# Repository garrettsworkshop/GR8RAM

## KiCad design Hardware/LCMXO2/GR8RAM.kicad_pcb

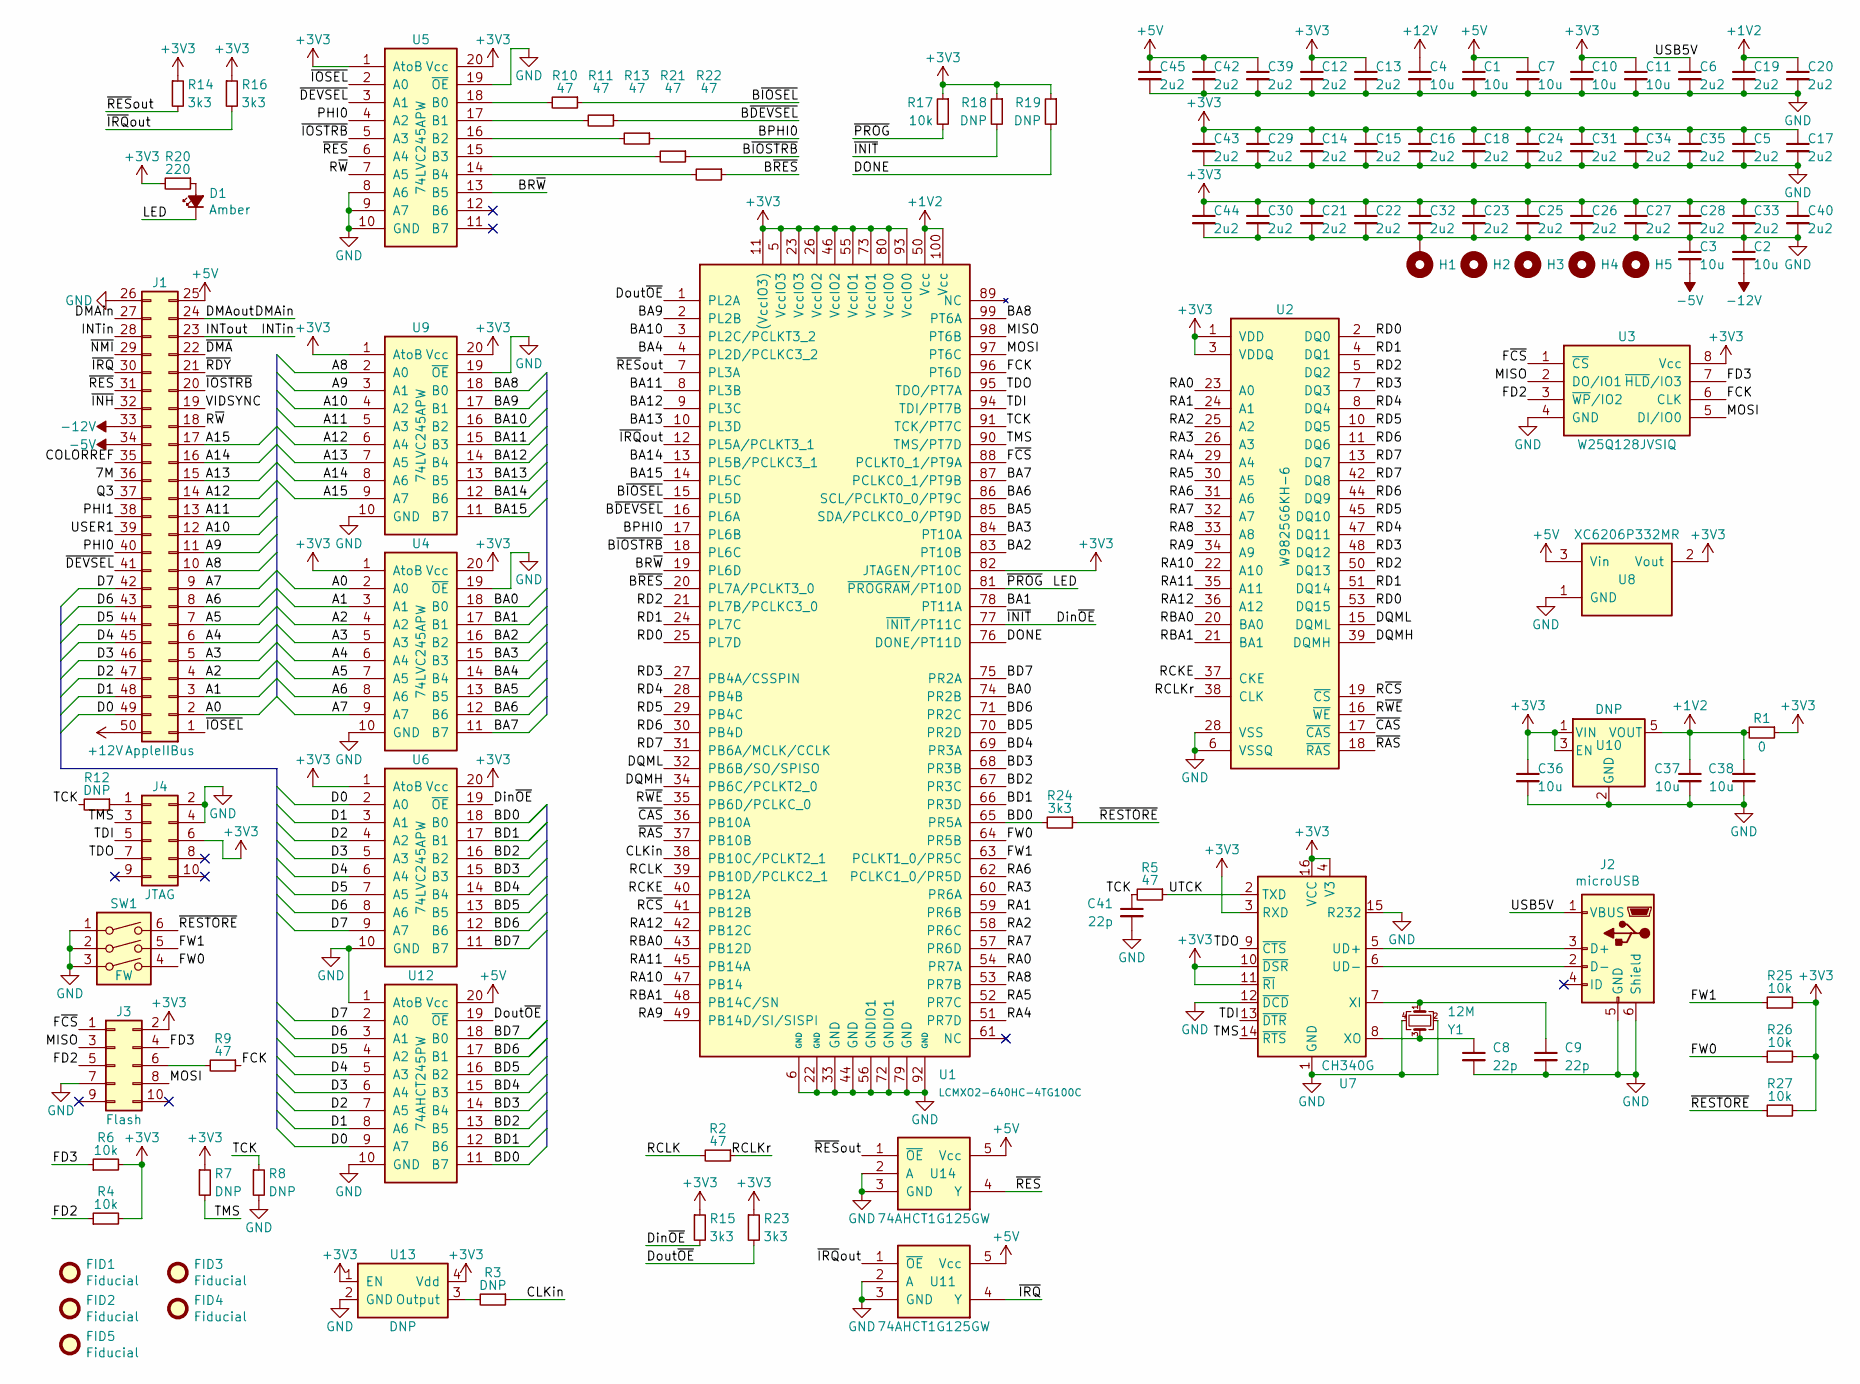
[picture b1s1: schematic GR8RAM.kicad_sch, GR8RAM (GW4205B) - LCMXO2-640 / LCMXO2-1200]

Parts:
C1, C2, C3, C4, C7, C10, C11, C36, C37, C38: 10u; C_0805; LCSC Part C15850
C5, C6, C12, C13, C14, C15, C16, C17, C18, C19, C20, C21, C22, C23, C24, C25, C26, C27, C28, C29, C30, C31, C32, C33, C34, C35, C39, C40, C42, C43, C44, C45: 2u2; C_0603; LCSC Part C23630
C8, C9, C41: 22p; C_0603; LCSC Part C1653
D1: Amber; LED_0805; LCSC Part C284932
FID1, FID2, FID3, FID4, FID5: Fiducial
H1: PasteHole_1.1mm_PTH
H2, H3, H4, H5: PasteHole_1.152mm_NPTH
J1: AppleIIBus; AppleIIBus_Edge
J2: microUSB; USB_Micro-B_Amphenol_10118192-0001; LCSC Part C132564
J3: Flash; Tag-Connect_TC2050-IDC-FP_2x05_P1.27mm_Vertical
J4: JTAG; Tag-Connect_TC2050-IDC-FP_2x05_P1.27mm_Vertical
R1: 0; R_0805; LCSC Part C17477
R2, R5, R9, R10, R11, R13, R21, R22: 47; R_0603; LCSC Part C23182
R3, R7, R8, R12, R18, R19: DNP; R_0603
R4, R6, R17, R25, R26, R27: 10k; R_0603; LCSC Part C25804
R14, R15, R16, R23, R24: 3k3; R_0603; LCSC Part C22978
R20: 220; R_0805; LCSC Part C17557
SW1: FW; SW_DIP_SPSTx03_Slide_DSHP03TS_P1.27mm; LCSC Part C319051
U1: LCMXO2-640HC-4TG100C; TQFP-100_14x14mm_P0.5mm; LCSC Part C1519051
U2: W9825G6KH-6; TSOP-II-54_22.2x10.16mm_P0.8mm; LCSC Part C62246
U3: W25Q128JVSIQ; SOIC-8_5.3mm; LCSC Part C97521
U4, U5, U6, U9: 74LVC245APW; TSSOP-20_4.4x6.5mm_P0.65mm; LCSC Part C6082
U7: CH340G; SOIC-16_3.9mm; LCSC Part C14267
U8: XC6206P332MR; SOT-23; LCSC Part C5446
U10: DNP; SOT-23-5
U11, U14: 74AHCT1G125GW; SOT-353; LCSC Part C12495
U12: 74AHCT245PW; TSSOP-20_4.4x6.5mm_P0.65mm; LCSC Part C173388
U13: DNP; Crystal_SMD_3225-4Pin_3.2x2.5mm
Y1: 12M; Crystal_SMD_3225-4Pin_3.2x2.5mm; LCSC Part C9002

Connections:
+1V2: C19.1, C20.1, C37.1, C38.1, R1.2, U1.50 (Vcc), U1.100 (Vcc), U10.5 (VOUT)
+3V3: C5.1, C10.1, C11.1, C12.1, C13.1, C14.1, C15.1, C16.1, C17.1, C18.1, C21.1, C22.1, C23.1, C24.1, C25.1, C26.1, C27.1, C28.1, C29.1, C30.1, C31.1, C32.1, C33.1, C34.1, C35.1, C36.1, C40.1, C43.1, C44.1, J3.2, J4.6, R1.1, R4.2, R6.2, R7.1, R14.1, R15.1, R16.1, R17.1, R18.1, R19.1, R20.2, R23.1, R25.2, R26.2, R27.2, U1.5 (VccIO3), U1.11 ((VccIO3)), U1.23 (VccIO3), U1.26 (VccIO2), U1.46 (VccIO2), U1.55 (VccIO1), U1.73 (VccIO1), U1.80 (VccIO0), U1.82 (JTAGEN/PT10C), U1.93 (VccIO0), U2.1 (VDD), U2.3 (VDDQ), U2.9 (VDDQ), U2.14 (VDD), U2.27 (VDD), U2.43 (VDDQ), U2.49 (VDDQ), U3.8 (Vcc), U4.1 (AtoB), U4.20 (Vcc), U5.1 (AtoB), U5.20 (Vcc), U6.1 (AtoB), U6.20 (Vcc), U7.3 (RXD), U7.4 (V3), U7.10 (~DSR), U7.11 (~RI), U7.16 (VCC), U8.2 (Vout), U9.1 (AtoB), U9.20 (Vcc), U10.1 (VIN), U10.3 (EN), U13.1 (EN), U13.4 (Vdd)
+5V: C1.1, C7.1, C39.1, C42.1, C45.1, J1.25, U8.3 (Vin), U11.5 (Vcc), U12.20 (Vcc), U14.5 (Vcc)
+12V: C4.1, J1.50
-5V: C3.2, J1.34
-12V: C2.2, J1.33
/7M: J1.36
/A0: J1.2, U4.2 (A0)
/A1: J1.3, U4.3 (A1)
/A2: J1.4, U4.4 (A2)
/A3: J1.5, U4.5 (A3)
/A4: J1.6, U4.6 (A4)
/A5: J1.7, U4.7 (A5)
/A6: J1.8, U4.8 (A6)
/A7: J1.9, U4.9 (A7)
/A8: J1.10, U9.2 (A0)
/A9: J1.11, U9.3 (A1)
/A10: J1.12, U9.4 (A2)
/A11: J1.13, U9.5 (A3)
/A12: J1.14, U9.6 (A4)
/A13: J1.15, U9.7 (A5)
/A14: J1.16, U9.8 (A6)
/A15: J1.17, U9.9 (A7)
/BA0: U1.74 (PR2B), U4.18 (B0)
/BA1: U1.78 (PT11A), U4.17 (B1)
/BA2: U1.83 (PT10B), U4.16 (B2)
/BA3: U1.84 (PT10A), U4.15 (B3)
/BA4: U1.4 (PL2D/PCLKC3_2), U4.14 (B4)
/BA5: U1.85 (SDA/PCLKC0_0/PT9D), U4.13 (B5)
/BA6: U1.86 (SCL/PCLKT0_0/PT9C), U4.12 (B6)
/BA7: U1.87 (PCLKC0_1/PT9B), U4.11 (B7)
/BA8: U1.99 (PT6A), U9.18 (B0)
/BA9: U1.2 (PL2B), U9.17 (B1)
/BA10: U1.3 (PL2C/PCLKT3_2), U9.16 (B2)
/BA11: U1.8 (PL3B), U9.15 (B3)
/BA12: U1.9 (PL3C), U9.14 (B4)
/BA13: U1.10 (PL3D), U9.13 (B5)
/BA14: U1.13 (PL5B/PCLKC3_1), U9.12 (B6)
/BA15: U1.14 (PL5C), U9.11 (B7)
/BD0: R24.2, U1.65 (PR5A), U6.18 (B0), U12.11 (B7)
/BD1: U1.66 (PR3D), U6.17 (B1), U12.12 (B6)
/BD2: U1.67 (PR3C), U6.16 (B2), U12.13 (B5)
/BD3: U1.68 (PR3B), U6.15 (B3), U12.14 (B4)
/BD4: U1.69 (PR3A), U6.14 (B4), U12.15 (B3)
/BD5: U1.70 (PR2D), U6.13 (B5), U12.16 (B2)
/BD6: U1.71 (PR2C), U6.12 (B6), U12.17 (B1)
/BD7: U1.75 (PR2A), U6.11 (B7), U12.18 (B0)
/BPHI0: R13.1, U1.17 (PL6B)
/BR~W: U1.19 (PL6D), U5.13 (B5)
/B~DEVSEL: R11.1, U1.16 (PL6A)
/B~IOSEL: R10.1, U1.15 (PL5D)
/B~IOSTRB: R21.1, U1.18 (PL6C)
/B~RES: R22.1, U1.20 (PL7A/PCLKT3_0)
/CLKin: R3.1, U1.38 (PB10C/PCLKT2_1)
/COLORREF: J1.35
/D0: J1.49, U6.2 (A0), U12.9 (A7)
/D1: J1.48, U6.3 (A1), U12.8 (A6)
/D2: J1.47, U6.4 (A2), U12.7 (A5)
/D3: J1.46, U6.5 (A3), U12.6 (A4)
/D4: J1.45, U6.6 (A4), U12.5 (A3)
/D5: J1.44, U6.7 (A5), U12.4 (A2)
/D6: J1.43, U6.8 (A6), U12.3 (A1)
/D7: J1.42, U6.9 (A7), U12.2 (A0)
/DMAin: J1.24, J1.27
/DONE: R19.2, U1.76 (DONE/PT11D)
/DQMH: U1.34 (PB6C/PCLKT2_0), U2.39 (DQMH)
/DQML: U1.32 (PB6B/SO/SPISO), U2.15 (DQML)
/Din~OE: R15.2, R18.2, U1.77 (~INIT/PT11C), U6.19 (~OE)
/Dout~OE: R23.2, U1.1 (PL2A), U12.19 (~OE)
/FCK: R9.1, U1.96 (PT6D), U3.6 (CLK)
/FD2: J3.5, R4.1, U3.3 (~WP/IO2)
/FD3: J3.4, R6.1, U3.7 (~HLD/IO3)
/FW0: R26.1, SW1.4, U1.64 (PR5B)
/FW1: R25.1, SW1.5, U1.63 (PCLKT1_0/PR5C)
/F~CS: J3.1, U1.88 (PCLKT0_1/PT9A), U3.1 (~CS)
/INTin: J1.23, J1.28
/LED: D1.1 (K), R17.2, U1.81 (~PROGRAM/PT10D)
/MISO: J3.3, U1.98 (PT6B), U3.2 (DO/IO1)
/MOSI: J3.8, U1.97 (PT6C), U3.5 (DI/IO0)
/PHI0: J1.40, U5.4 (A2)
/PHI1: J1.38
/Q3: J1.37
/RA0: U1.54 (PR7A), U2.23 (A0)
/RA1: U1.59 (PR6B), U2.24 (A1)
/RA2: U1.58 (PR6C), U2.25 (A2)
/RA3: U1.60 (PR6A), U2.26 (A3)
/RA4: U1.51 (PR7D), U2.29 (A4)
/RA5: U1.52 (PR7C), U2.30 (A5)
/RA6: U1.62 (PCLKC1_0/PR5D), U2.31 (A6)
/RA7: U1.57 (PR6D), U2.32 (A7)
/RA8: U1.53 (PR7B), U2.33 (A8)
/RA9: U1.49 (PB14D/SI/SISPI), U2.34 (A9)
/RA10: U1.47 (PB14), U2.22 (A10)
/RA11: U1.45 (PB14A), U2.35 (A11)
/RA12: U1.42 (PB12C), U2.36 (A12)
/RBA0: U1.43 (PB12D), U2.20 (BA0)
/RBA1: U1.48 (PB14C/SN), U2.21 (BA1)
/RCKE: U1.40 (PB12A), U2.37 (CKE)
/RCLK: R2.2, U1.39 (PB10D/PCLKC2_1)
/RCLKr: R2.1, U2.38 (CLK)
/RD0: U1.25 (PL7D), U2.2 (DQ0), U2.53 (DQ15)
/RD1: U1.24 (PL7C), U2.4 (DQ1), U2.51 (DQ14)
/RD2: U1.21 (PL7B/PCLKC3_0), U2.5 (DQ2), U2.50 (DQ13)
/RD3: U1.27 (PB4A/CSSPIN), U2.7 (DQ3), U2.48 (DQ12)
/RD4: U1.28 (PB4B), U2.8 (DQ4), U2.47 (DQ11)
/RD5: U1.29 (PB4C), U2.10 (DQ5), U2.45 (DQ10)
/RD6: U1.30 (PB4D), U2.11 (DQ6), U2.44 (DQ9)
/RD7: U1.31 (PB6A/MCLK/CCLK), U2.13 (DQ7), U2.42 (DQ8)
/R~CS: U1.41 (PB12B), U2.19 (~CS)
/R~WE: U1.35 (PB6D/PCLKC_0), U2.16 (~WE)
/R~W: J1.18, U5.7 (A5)
/TCK: C41.1, R5.2, R8.1, R12.2, U1.91 (TCK/PT7C)
/TDI: J4.5, U1.94 (TDI/PT7B), U7.13 (~DTR)
/TDO: J4.7, U1.95 (TDO/PT7A), U7.9 (~CTS)
/TMS: J4.3, R7.2, U1.90 (TMS/PT7D), U7.14 (~RTS)
/USB5V: C6.1, J2.1 (VBUS)
/USER1: J1.39
/UTCK: R5.1, U7.2 (TXD)
/VIDSYNC: J1.19
/~CAS: U1.36 (PB10A), U2.17 (~CAS)
/~DEVSEL: J1.41, U5.3 (A1)
/~DMA: J1.22
/~INH: J1.32
/~IOSEL: J1.1, U5.2 (A0)
/~IOSTRB: J1.20, U5.5 (A3)
/~IRQ: J1.30, U11.4 (Y)
/~IRQout: R16.2, U1.12 (PL5A/PCLKT3_1), U11.1 (~OE)
/~NMI: J1.29
/~RAS: U1.37 (PB10B), U2.18 (~RAS)
/~RDY: J1.21
/~RESTORE: R24.1, R27.1, SW1.6
/~RES: J1.31, U5.6 (A4), U14.4 (Y)
/~RESout: R14.2, U1.7 (PL3A), U14.1 (~OE)
GND: C1.2, C2.1, C3.1, C4.2, C5.2, C6.2, C7.2, C8.2, C9.2, C10.2, C11.2, C12.2, C13.2, C14.2, C15.2, C16.2, C17.2, C18.2, C19.2, C20.2, C21.2, C22.2, C23.2, C24.2, C25.2, C26.2, C27.2, C28.2, C29.2, C30.2, C31.2, C32.2, C33.2, C34.2, C35.2, C36.2, C37.2, C38.2, C39.2, C40.2, C41.2, C42.2, C43.2, C44.2, C45.2, H1.1, J1.26, J2.5 (GND), J2.6 (Shield), J3.7, J4.2, J4.4, R8.2, SW1.1, SW1.2, SW1.3, U1.6 (GND), U1.22 (GND), U1.33 (GND), U1.44 (GND), U1.56 (GNDIO1), U1.72 (GNDIO1), U1.79 (GND), U1.92 (GND), U2.6 (VSSQ), U2.12 (VSSQ), U2.28 (VSS), U2.41 (VSS), U2.46 (VSSQ), U2.52 (VSSQ), U2.54 (VSS), U3.4 (GND), U4.10 (GND), U4.19 (~OE), U5.8 (A6), U5.9 (A7), U5.10 (GND), U5.19 (~OE), U6.10 (GND), U7.1 (GND), U7.12 (~DCD), U7.15 (R232), U8.1 (GND), U9.10 (GND), U9.19 (~OE), U10.2 (GND), U11.2 (A), U11.3 (GND), U12.1 (AtoB), U12.10 (GND), U13.2 (GND), U14.2 (A), U14.3 (GND), Y1.2, Y1.4
unnamed: D1.2 (A), R20.1
unnamed: J2.3 (D+), U7.5 (UD+)
unnamed: J2.2 (D-), U7.6 (UD-)
unnamed: J3.6, R9.2
unnamed: J4.1, R12.1
unnamed: R10.2, U5.18 (B0)
unnamed: R11.2, U5.17 (B1)
unnamed: R13.2, U5.16 (B2)
unnamed: R21.2, U5.15 (B3)
unnamed: R22.2, U5.14 (B4)
unnamed: C9.1, U7.7 (XI), Y1.1
unnamed: C8.1, U7.8 (XO), Y1.3
unnamed: R3.2, U13.3 (Output)

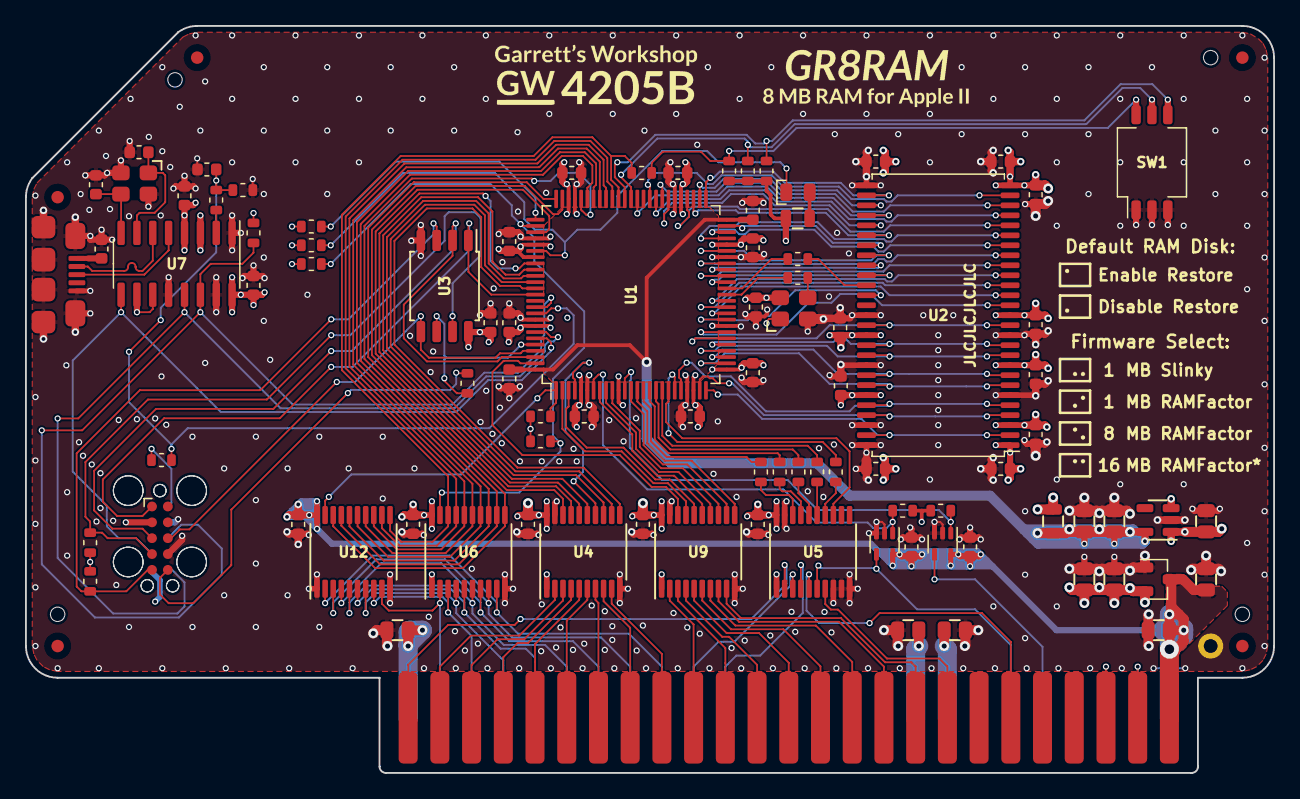
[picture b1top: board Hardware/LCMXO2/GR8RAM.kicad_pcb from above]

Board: 4 copper layers, 99.9 x 59.8 mm, 103 parts (1 on the bottom side), 137 nets.

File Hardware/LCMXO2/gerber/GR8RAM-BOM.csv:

"Reference","Quantity","Value","Footprint","LCSC Part","DNP"
"C1, C2, C3, C4, C7, C10, C11, C36, C37, C38","10","10u","stdpads:C_0805","C15850",""
"C5, C6, C12, C13, C14, C15, C16, C17, C18, C19, C20, C21, C22, C23, C24, C25, C26, C27, C28, C29, C30, C31, C32, C33, C34, C35, C39, C40, C42, C43, C44, C45","32","2u2","stdpads:C_0603","C23630",""
"C8, C9, C41","3","22p","stdpads:C_0603","C1653",""
"D1","1","Amber","stdpads:LED_0805","C284932",""
"FID1, FID2, FID3, FID4, FID5","5","Fiducial","stdpads:Fiducial","",""
"H1","1","","stdpads:PasteHole_1.1mm_PTH","",""
"H2, H3, H4, H5","4","","stdpads:PasteHole_1.152mm_NPTH","",""
"J1","1","AppleIIBus","stdpads:AppleIIBus_Edge","",""
"J2","1","microUSB","stdpads:USB_Micro-B_Amphenol_10118192-0001","C132564",""
"J3","1","Flash","stdpads:Tag-Connect_TC2050-IDC-FP_2x05_P1.27mm_Vertical","",""
"J4","1","JTAG","stdpads:Tag-Connect_TC2050-IDC-FP_2x05_P1.27mm_Vertical","",""
"R1","1","0","stdpads:R_0805","C17477",""
"R2, R3, R5, R9, R10, R11, R13, R21, R22","9","47","stdpads:R_0603","C23182",""
"R4, R6, R15, R17, R25, R26, R27","7","10k","stdpads:R_0603","C25804",""
"R7, R8, R12, R18, R19","5","DNP","stdpads:R_0603","",""
"R14, R16, R23, R24","4","2k2","stdpads:R_0603","C4190",""
"R20","1","220","stdpads:R_0805","C17557",""
"SW1","1","FW","stdpads:SW_DIP_SPSTx03_Slide_DSHP03TS_P1.27mm","C319052",""
"U1","1","LCMXO2-640HC-4TG100C","stdpads:TQFP-100_14x14mm_P0.5mm","C1519051",""
"U2","1","W9825G6KH-6","stdpads:TSOP-II-54_22.2x10.16mm_P0.8mm","C62246",""
"U3","1","W25Q128JVSIQ","stdpads:SOIC-8_5.3mm","C97521",""
"U4, U5, U9","3","74LVC245APW","stdpads:TSSOP-20_4.4x6.5mm_P0.65mm","C6082",""
"U6","1","74AHC245PW","stdpads:TSSOP-20_4.4x6.5mm_P0.65mm","C5516",""
"U7","1","CH340G","stdpads:SOIC-16_3.9mm","C14267",""
"U8","1","XC6206P332MR","stdpads:SOT-23","C5446",""
"U10","1","AP2127K-1.2TRG1","stdpads:SOT-23-5","C151376",""
"U11, U14","2","74AHCT1G125GW","stdpads:SOT-353","C12495",""
"U12","1","74AHCT245PW","stdpads:TSSOP-20_4.4x6.5mm_P0.65mm","C5516",""
"U13","1","25M","stdpads:Crystal_SMD_3225-4Pin_3.2x2.5mm","C669088",""
"Y1","1","12M","stdpads:Crystal_SMD_3225-4Pin_3.2x2.5mm","C9002",""

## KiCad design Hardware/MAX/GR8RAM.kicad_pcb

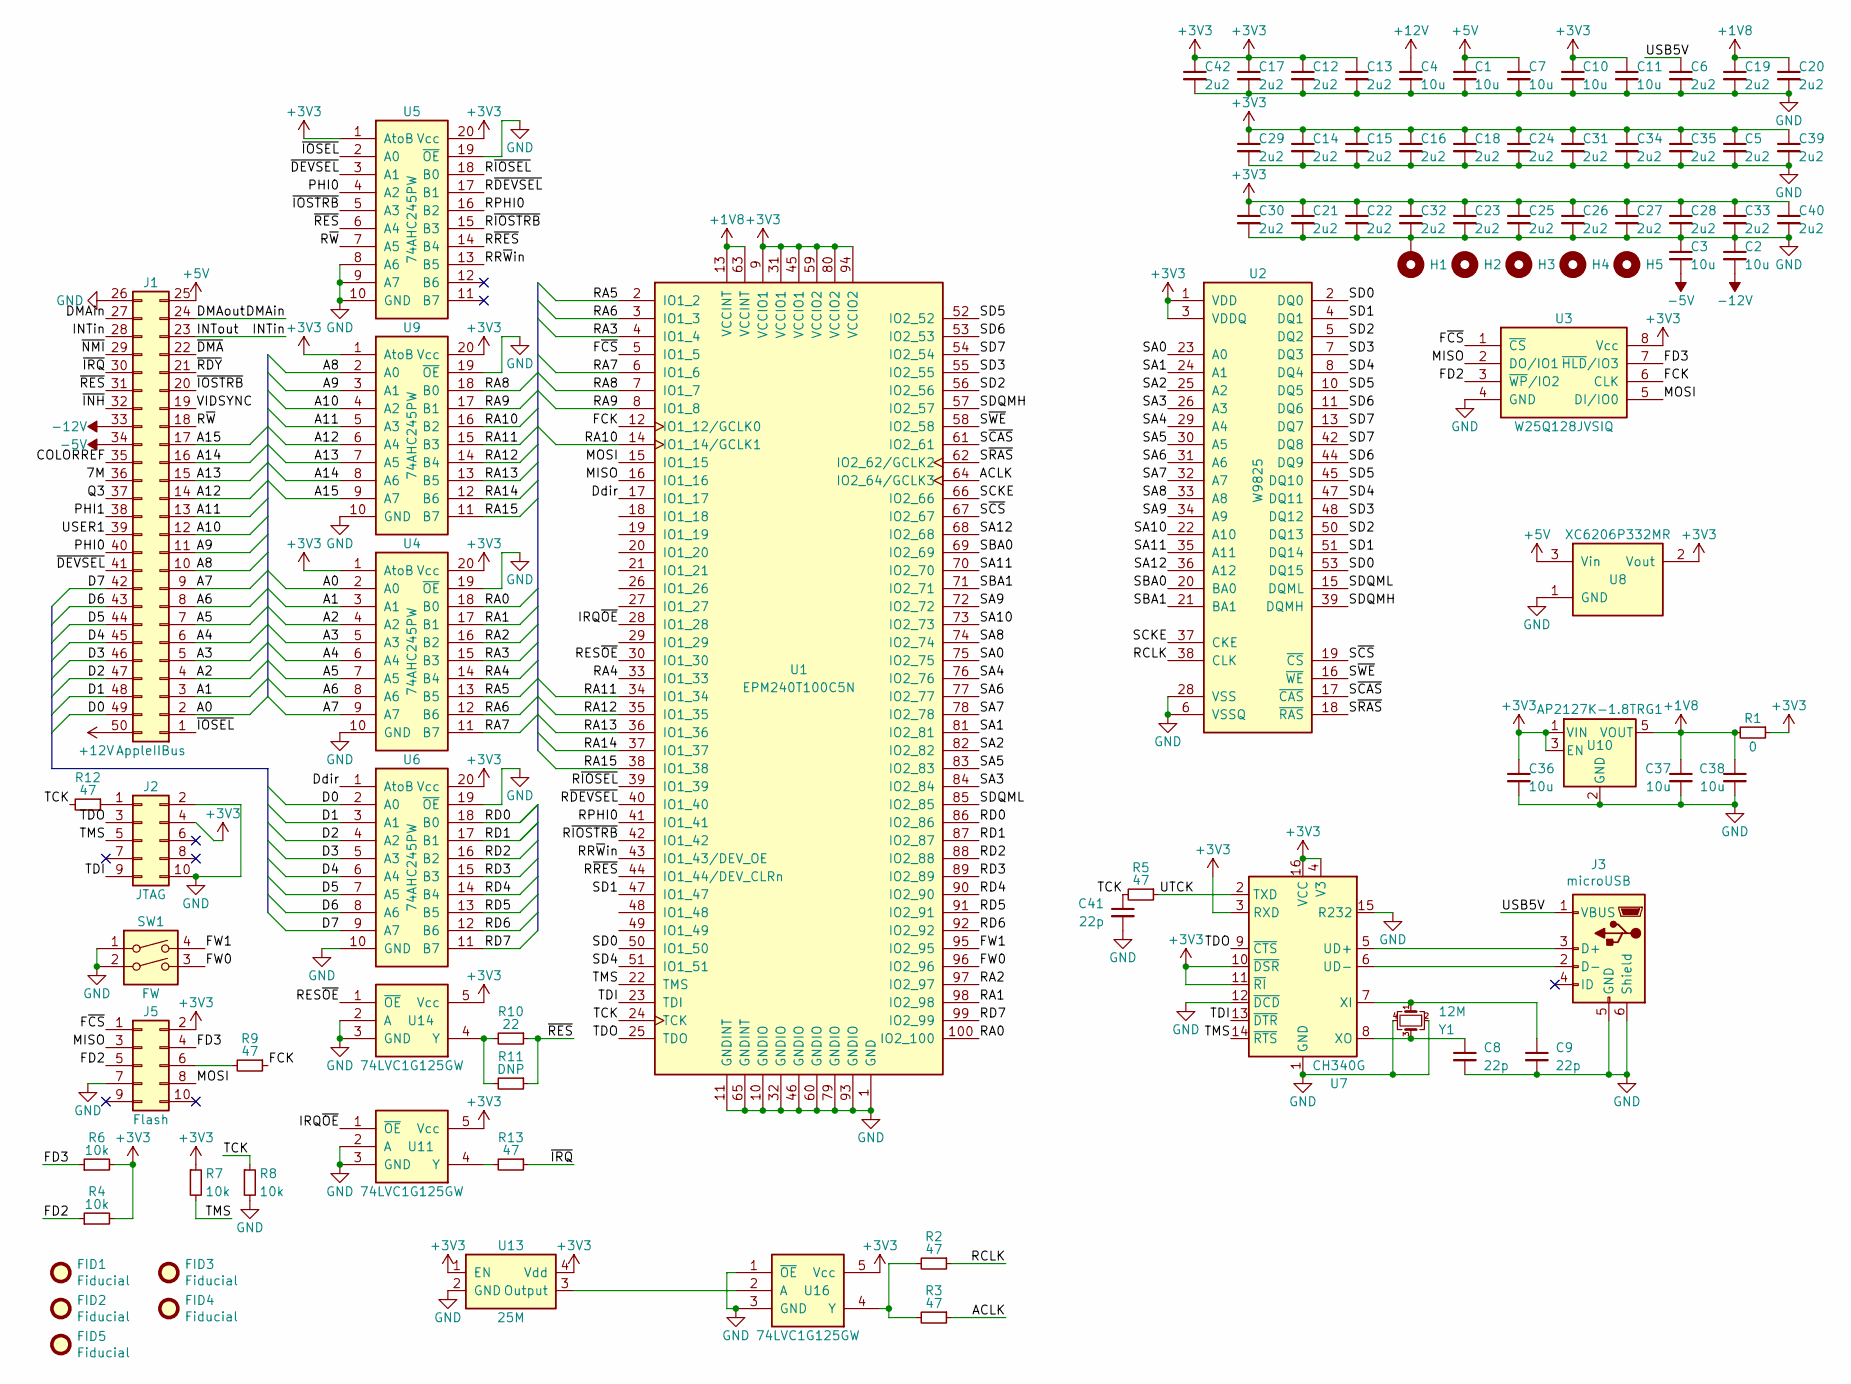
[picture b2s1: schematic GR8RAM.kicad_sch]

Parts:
C1, C2, C3, C4, C7, C10, C11, C36, C37, C38: 10u; C_0805; LCSC Part C15850
C5, C6, C12, C13, C14, C15, C16, C17, C18, C19, C20, C21, C22, C23, C24, C25, C26, C27, C28, C29, C30, C31, C32, C33, C34, C35, C39, C40, C42: 2u2; C_0603; LCSC Part C23630
C8, C9, C41: 22p; C_0603; LCSC Part C1653
FID1, FID2, FID3, FID4, FID5: Fiducial
H1: PasteHole_1.1mm_PTH
H2, H3, H4, H5: PasteHole_1.152mm_NPTH
J1: AppleIIBus; AppleIIBus_Edge
J2: JTAG; Tag-Connect_TC2050-IDC-FP_2x05_P1.27mm_Vertical
J3: microUSB; USB_Micro-B_Amphenol_10118192-0001; LCSC Part C132564
J5: Flash; Tag-Connect_TC2050-IDC-FP_2x05_P1.27mm_Vertical
R1: 0; R_0805; LCSC Part C17477
R2, R3, R5, R9, R12: 47; R_0603; LCSC Part C23182
R4, R6, R7, R8: 10k; R_0603; LCSC Part C25804
R10: 22; R_0603; LCSC Part C23345
R11: DNP; R_0603
R13: 47; R_0603; LCSC Part C23345
SW1: FW; SW_DIP_SPSTx02_Slide_DSHP02TS_P1.27mm; LCSC Part C319052
U1: EPM240T100C5N; TQFP-100_14x14mm_P0.5mm; LCSC Part C10041
U2: W9825; TSOP-II-54_22.2x10.16mm_P0.8mm; LCSC Part C62246
U3: W25Q128JVSIQ; SOIC-8_5.3mm; LCSC Part C97521
U4, U5, U6, U9: 74AHC245PW; TSSOP-20_4.4x6.5mm_P0.65mm; LCSC Part C5516
U7: CH340G; SOIC-16_3.9mm; LCSC Part C14267
U8: XC6206P332MR; SOT-23; LCSC Part C5446
U10: AP2127K-1.8TRG1; SOT-23-5; LCSC Part C151375
U11, U14, U16: 74LVC1G125GW; SOT-353; LCSC Part C12519
U13: 25M; Crystal_SMD_3225-4Pin_3.2x2.5mm; LCSC Part C669088
Y1: 12M; Crystal_SMD_3225-4Pin_3.2x2.5mm; LCSC Part C9002

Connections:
+1V8: C19.1, C20.1, C37.1, C38.1, R1.2, U1.13 (VCCINT), U1.63 (VCCINT), U10.5 (VOUT)
+3V3: C5.1, C10.1, C11.1, C12.1, C13.1, C14.1, C15.1, C16.1, C17.1, C18.1, C21.1, C22.1, C23.1, C24.1, C25.1, C26.1, C27.1, C28.1, C29.1, C30.1, C31.1, C32.1, C33.1, C34.1, C35.1, C36.1, C39.1, C40.1, C42.1, J2.4, J5.2, R1.1, R4.2, R6.2, R7.1, U1.9 (VCCIO1), U1.31 (VCCIO1), U1.45 (VCCIO1), U1.59 (VCCIO2), U1.80 (VCCIO2), U1.94 (VCCIO2), U2.1 (VDD), U2.3 (VDDQ), U2.9 (VDDQ), U2.14 (VDD), U2.27 (VDD), U2.43 (VDDQ), U2.49 (VDDQ), U3.8 (Vcc), U4.1 (AtoB), U4.20 (Vcc), U5.1 (AtoB), U5.20 (Vcc), U6.20 (Vcc), U7.3 (RXD), U7.4 (V3), U7.10 (~DSR), U7.11 (~RI), U7.16 (VCC), U8.2 (Vout), U9.1 (AtoB), U9.20 (Vcc), U10.1 (VIN), U10.3 (EN), U11.5 (Vcc), U13.1 (EN), U13.4 (Vdd), U14.5 (Vcc), U16.5 (Vcc)
+5V: C1.1, C7.1, J1.25, U8.3 (Vin)
+12V: C4.1, J1.50
-5V: C3.2, J1.34
-12V: C2.2, J1.33
/7M: J1.36
/A0: J1.2, U4.2 (A0)
/A1: J1.3, U4.3 (A1)
/A2: J1.4, U4.4 (A2)
/A3: J1.5, U4.5 (A3)
/A4: J1.6, U4.6 (A4)
/A5: J1.7, U4.7 (A5)
/A6: J1.8, U4.8 (A6)
/A7: J1.9, U4.9 (A7)
/A8: J1.10, U9.2 (A0)
/A9: J1.11, U9.3 (A1)
/A10: J1.12, U9.4 (A2)
/A11: J1.13, U9.5 (A3)
/A12: J1.14, U9.6 (A4)
/A13: J1.15, U9.7 (A5)
/A14: J1.16, U9.8 (A6)
/A15: J1.17, U9.9 (A7)
/ACLK: R3.1, U1.64 (IO2_64/GCLK3)
/COLORREF: J1.35
/D0: J1.49, U6.2 (A0)
/D1: J1.48, U6.3 (A1)
/D2: J1.47, U6.4 (A2)
/D3: J1.46, U6.5 (A3)
/D4: J1.45, U6.6 (A4)
/D5: J1.44, U6.7 (A5)
/D6: J1.43, U6.8 (A6)
/D7: J1.42, U6.9 (A7)
/DMAin: J1.24, J1.27
/Ddir: U1.17 (IO1_17), U6.1 (AtoB)
/FCK: R9.1, U1.12 (IO1_12/GCLK0), U3.6 (CLK)
/FD2: J5.5, R4.1, U3.3 (~WP/IO2)
/FD3: J5.4, R6.1, U3.7 (~HLD/IO3)
/FW0: SW1.3, U1.96 (IO2_96)
/FW1: SW1.4, U1.95 (IO2_95)
/F~CS: J5.1, U1.5 (IO1_5), U3.1 (~CS)
/INTin: J1.23, J1.28
/IRQ~OE: U1.28 (IO1_28), U11.1 (~OE)
/MISO: J5.3, U1.16 (IO1_16), U3.2 (DO/IO1)
/MOSI: J5.8, U1.15 (IO1_15), U3.5 (DI/IO0)
/PHI0: J1.40, U5.4 (A2)
/PHI1: J1.38
/Q3: J1.37
/RA0: U1.100 (IO2_100), U4.18 (B0)
/RA1: U1.98 (IO2_98), U4.17 (B1)
/RA2: U1.97 (IO2_97), U4.16 (B2)
/RA3: U1.4 (IO1_4), U4.15 (B3)
/RA4: U1.33 (IO1_33), U4.14 (B4)
/RA5: U1.2 (IO1_2), U4.13 (B5)
/RA6: U1.3 (IO1_3), U4.12 (B6)
/RA7: U1.6 (IO1_6), U4.11 (B7)
/RA8: U1.7 (IO1_7), U9.18 (B0)
/RA9: U1.8 (IO1_8), U9.17 (B1)
/RA10: U1.14 (IO1_14/GCLK1), U9.16 (B2)
/RA11: U1.34 (IO1_34), U9.15 (B3)
/RA12: U1.35 (IO1_35), U9.14 (B4)
/RA13: U1.36 (IO1_36), U9.13 (B5)
/RA14: U1.37 (IO1_37), U9.12 (B6)
/RA15: U1.38 (IO1_38), U9.11 (B7)
/RCLK: R2.1, U2.38 (CLK)
/RD0: U1.86 (IO2_86), U6.18 (B0)
/RD1: U1.87 (IO2_87), U6.17 (B1)
/RD2: U1.88 (IO2_88), U6.16 (B2)
/RD3: U1.89 (IO2_89), U6.15 (B3)
/RD4: U1.90 (IO2_90), U6.14 (B4)
/RD5: U1.91 (IO2_91), U6.13 (B5)
/RD6: U1.92 (IO2_92), U6.12 (B6)
/RD7: U1.99 (IO2_99), U6.11 (B7)
/RES~OE: U1.30 (IO1_30), U14.1 (~OE)
/RPHI0: U1.41 (IO1_41), U5.16 (B2)
/RR~Win: U1.43 (IO1_43/DEV_OE), U5.13 (B5)
/R~DEVSEL: U1.40 (IO1_40), U5.17 (B1)
/R~IOSEL: U1.39 (IO1_39), U5.18 (B0)
/R~IOSTRB: U1.42 (IO1_42), U5.15 (B3)
/R~RES: U1.44 (IO1_44/DEV_CLRn), U5.14 (B4)
/R~W: J1.18, U5.7 (A5)
/SA0: U1.75 (IO2_75), U2.23 (A0)
/SA1: U1.81 (IO2_81), U2.24 (A1)
/SA2: U1.82 (IO2_82), U2.25 (A2)
/SA3: U1.84 (IO2_84), U2.26 (A3)
/SA4: U1.76 (IO2_76), U2.29 (A4)
/SA5: U1.83 (IO2_83), U2.30 (A5)
/SA6: U1.77 (IO2_77), U2.31 (A6)
/SA7: U1.78 (IO2_78), U2.32 (A7)
/SA8: U1.74 (IO2_74), U2.33 (A8)
/SA9: U1.72 (IO2_72), U2.34 (A9)
/SA10: U1.73 (IO2_73), U2.22 (A10)
/SA11: U1.70 (IO2_70), U2.35 (A11)
/SA12: U1.68 (IO2_68), U2.36 (A12)
/SBA0: U1.69 (IO2_69), U2.20 (BA0)
/SBA1: U1.71 (IO2_71), U2.21 (BA1)
/SCKE: U1.66 (IO2_66), U2.37 (CKE)
/SD0: U1.50 (IO1_50), U2.2 (DQ0), U2.53 (DQ15)
/SD1: U1.47 (IO1_47), U2.4 (DQ1), U2.51 (DQ14)
/SD2: U1.56 (IO2_56), U2.5 (DQ2), U2.50 (DQ13)
/SD3: U1.55 (IO2_55), U2.7 (DQ3), U2.48 (DQ12)
/SD4: U1.51 (IO1_51), U2.8 (DQ4), U2.47 (DQ11)
/SD5: U1.52 (IO2_52), U2.10 (DQ5), U2.45 (DQ10)
/SD6: U1.53 (IO2_53), U2.11 (DQ6), U2.44 (DQ9)
/SD7: U1.54 (IO2_54), U2.13 (DQ7), U2.42 (DQ8)
/SDQMH: U1.57 (IO2_57), U2.39 (DQMH)
/SDQML: U1.85 (IO2_85), U2.15 (DQML)
/S~CAS: U1.61 (IO2_61), U2.17 (~CAS)
/S~CS: U1.67 (IO2_67), U2.19 (~CS)
/S~RAS: U1.62 (IO2_62/GCLK2), U2.18 (~RAS)
/S~WE: U1.58 (IO2_58), U2.16 (~WE)
/TCK: C41.1, R5.2, R8.1, R12.2, U1.24 (TCK)
/TDI: J2.9, U1.23 (TDI), U7.13 (~DTR)
/TDO: J2.3, U1.25 (TDO), U7.9 (~CTS)
/TMS: J2.5, R7.2, U1.22 (TMS), U7.14 (~RTS)
/USB5V: C6.1, J3.1 (VBUS)
/USER1: J1.39
/UTCK: R5.1, U7.2 (TXD)
/VIDSYNC: J1.19
/~DEVSEL: J1.41, U5.3 (A1)
/~DMA: J1.22
/~INH: J1.32
/~IOSEL: J1.1, U5.2 (A0)
/~IOSTRB: J1.20, U5.5 (A3)
/~IRQ: J1.30, R13.1
/~NMI: J1.29
/~RDY: J1.21
/~RES: J1.31, R10.1, R11.1, U5.6 (A4)
GND: C1.2, C2.1, C3.1, C4.2, C5.2, C6.2, C7.2, C8.2, C9.2, C10.2, C11.2, C12.2, C13.2, C14.2, C15.2, C16.2, C17.2, C18.2, C19.2, C20.2, C21.2, C22.2, C23.2, C24.2, C25.2, C26.2, C27.2, C28.2, C29.2, C30.2, C31.2, C32.2, C33.2, C34.2, C35.2, C36.2, C37.2, C38.2, C39.2, C40.2, C41.2, C42.2, H1.1, J1.26, J2.2, J2.10, J3.5 (GND), J3.6 (Shield), J5.7, R8.2, SW1.1, SW1.2, U1.1 (GND), U1.10 (GNDIO), U1.11 (GNDINT), U1.32 (GNDIO), U1.46 (GNDIO), U1.60 (GNDIO), U1.65 (GNDINT), U1.79 (GNDIO), U1.93 (GNDIO), U2.6 (VSSQ), U2.12 (VSSQ), U2.28 (VSS), U2.41 (VSS), U2.46 (VSSQ), U2.52 (VSSQ), U2.54 (VSS), U3.4 (GND), U4.10 (GND), U4.19 (~OE), U5.8 (A6), U5.9 (A7), U5.10 (GND), U5.19 (~OE), U6.10 (GND), U6.19 (~OE), U7.1 (GND), U7.12 (~DCD), U7.15 (R232), U8.1 (GND), U9.10 (GND), U9.19 (~OE), U10.2 (GND), U11.2 (A), U11.3 (GND), U13.2 (GND), U14.2 (A), U14.3 (GND), U16.1 (~OE), U16.3 (GND), Y1.2, Y1.4
unnamed: J2.1, R12.1
unnamed: J3.3 (D+), U7.5 (UD+)
unnamed: J3.2 (D-), U7.6 (UD-)
unnamed: J5.6, R9.2
unnamed: C9.1, U7.7 (XI), Y1.1
unnamed: C8.1, U7.8 (XO), Y1.3
unnamed: R13.2, U11.4 (Y)
unnamed: U13.3 (Output), U16.2 (A)
unnamed: R10.2, R11.2, U14.4 (Y)
unnamed: R2.2, R3.2, U16.4 (Y)

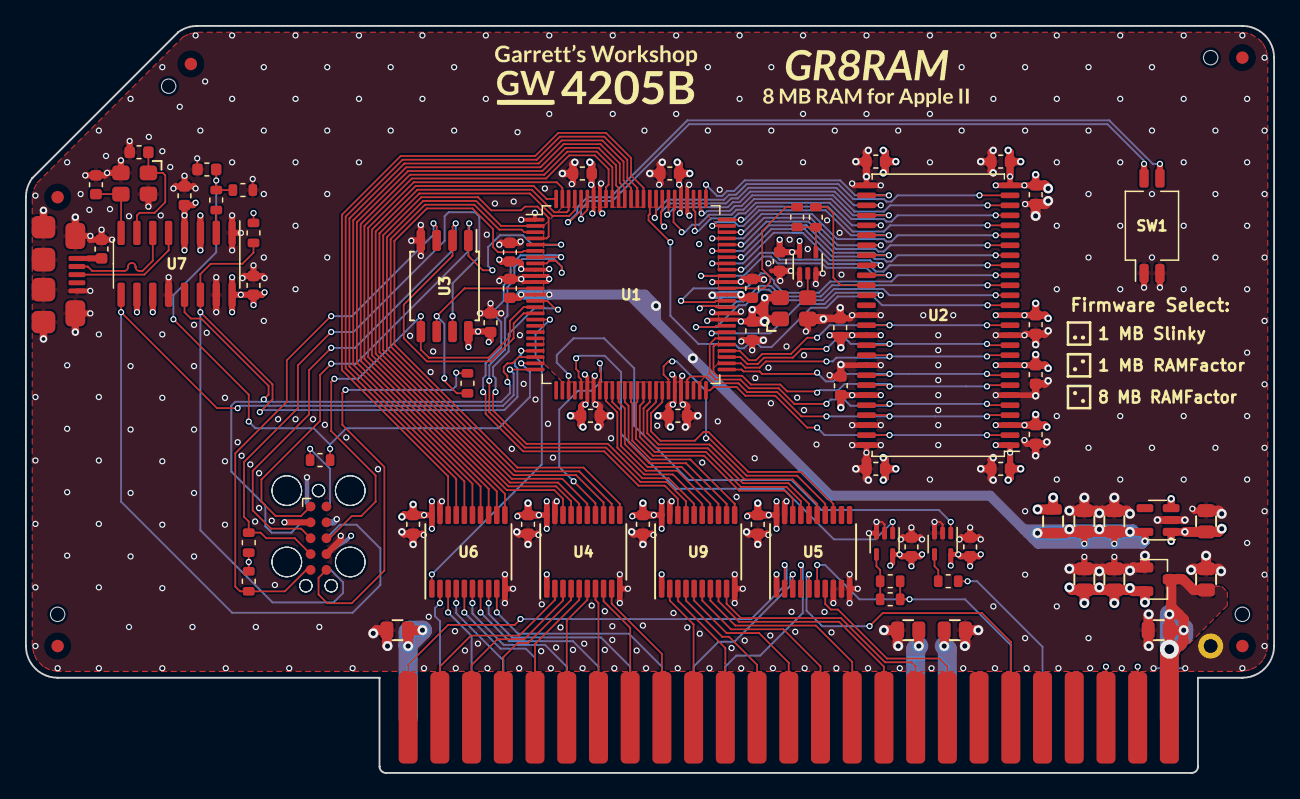
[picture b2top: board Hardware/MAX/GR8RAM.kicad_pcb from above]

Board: 4 copper layers, 99.9 x 59.8 mm, 85 parts (1 on the bottom side), 129 nets.

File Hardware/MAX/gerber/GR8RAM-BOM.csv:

"Reference","Quantity","Value","Footprint","LCSC Part","DNP"
"C1, C2, C3, C4, C7, C10, C11, C36, C37, C38","10","10u","stdpads:C_0805","C15850",""
"C5, C6, C12, C13, C14, C15, C16, C17, C18, C19, C20, C21, C22, C23, C24, C25, C26, C27, C28, C29, C30, C31, C32, C33, C34, C35, C39, C40, C42","29","2u2","stdpads:C_0603","C23630",""
"C8, C9, C41","3","22p","stdpads:C_0603","C1653",""
"FID1, FID2, FID3, FID4, FID5","5","Fiducial","stdpads:Fiducial","",""
"H1","1","","stdpads:PasteHole_1.1mm_PTH","",""
"H2, H3, H4, H5","4","","stdpads:PasteHole_1.152mm_NPTH","",""
"J1","1","AppleIIBus","stdpads:AppleIIBus_Edge","",""
"J2","1","JTAG","Connector:Tag-Connect_TC2050-IDC-FP_2x05_P1.27mm_Vertical","",""
"J3","1","microUSB","stdpads:USB_Micro-B_Amphenol_10118192-0001","C132564",""
"J5","1","Flash","Connector:Tag-Connect_TC2050-IDC-FP_2x05_P1.27mm_Vertical","",""
"R1","1","0","stdpads:R_0805","C17477",""
"R2, R3, R5, R9, R12, R13","6","47","stdpads:R_0603","C23345",""
"R4, R6, R7, R8","4","10k","stdpads:R_0603","C25804",""
"R10","1","22","stdpads:R_0603","C23345",""
"R11","1","DNP","stdpads:R_0603","",""
"SW1","1","FW","stdpads:SW_DIP_SPSTx02_Slide_DSHP02TS_P1.27mm","C319052",""
"U1","1","EPM240T100C5N","stdpads:TQFP-100_14x14mm_P0.5mm","C10041",""
"U2","1","W9825","stdpads:TSOP-II-54_22.2x10.16mm_P0.8mm","C62246",""
"U3","1","W25Q128JVSIQ","stdpads:SOIC-8_5.3mm","C97521",""
"U4, U5, U6, U9","4","74AHC245PW","stdpads:TSSOP-20_4.4x6.5mm_P0.65mm","C5516",""
"U7","1","CH340G","stdpads:SOIC-16_3.9mm","C14267",""
"U8","1","XC6206P332MR","stdpads:SOT-23","C5446",""
"U10","1","AP2127K-1.8TRG1","stdpads:SOT-23-5","C151375",""
"U11, U14, U16","3","74LVC1G125GW","stdpads:SOT-353","C12519",""
"U13","1","25M","stdpads:Crystal_SMD_3225-4Pin_3.2x2.5mm","C669088",""
"Y1","1","12M","stdpads:Crystal_SMD_3225-4Pin_3.2x2.5mm","C9002",""

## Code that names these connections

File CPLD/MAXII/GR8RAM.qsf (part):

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set_location_assignment PIN_6 -to RA[7]
set_location_assignment PIN_7 -to RA[8]
set_location_assignment PIN_8 -to RA[9]
set_location_assignment PIN_12 -to FCK
set_location_assignment PIN_14 -to RA[10]
set_location_assignment PIN_15 -to MOSI
set_location_assignment PIN_16 -to MISO
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set_location_assignment PIN_39 -to nIOSEL
set_location_assignment PIN_42 -to nIOSTRB
set_location_assignment PIN_40 -to nDEVSEL
set_location_assignment PIN_41 -to PHI0
set_location_assignment PIN_43 -to nWE
set_location_assignment PIN_44 -to nRES
set_location_assignment PIN_47 -to SD[1]
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set_location_assignment PIN_55 -to SD[3]
set_location_assignment PIN_56 -to SD[2]
set_location_assignment PIN_53 -to SD[6]
set_location_assignment PIN_57 -to DQMH
set_location_assignment PIN_58 -to nSWE
set_location_assignment PIN_62 -to nRAS
set_location_assignment PIN_61 -to nCAS
set_location_assignment PIN_64 -to C25M
set_location_assignment PIN_66 -to RCKE
set_location_assignment PIN_67 -to nRCS
set_location_assignment PIN_68 -to SA[12]
set_location_assignment PIN_69 -to SBA[0]
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set_location_assignment PIN_82 -to SA[2]
set_location_assignment PIN_83 -to SA[5]
set_location_assignment PIN_84 -to SA[3]
set_location_assignment PIN_85 -to DQML
set_location_assignment PIN_86 -to RD[0]
set_location_assignment PIN_87 -to RD[1]
set_location_assignment PIN_88 -to RD[2]
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set_location_assignment PIN_28 -to nRDYout
set_location_assignment PIN_29 -to nIRQout
set_location_assignment PIN_33 -to RWout
set_location_assignment PIN_48 -to DMAin
set_location_assignment PIN_49 -to INTin
set_location_assignment PIN_17 -to RDdir
set_location_assignment PIN_18 -to DMAout
set_instance_assignment -name IO_STANDARD "3.3-V LVTTL" -to RA
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
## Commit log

2019-06-25 Rough schematic and board layout
2019-07-21 Release candidate PCB
2019-07-30 Submitted to JLCPCB
2019-09-01 CPLD firmware compiles
2019-09-02 1MB CPLD design seems to work, fails Apple BIST
2019-09-02 Clarifications and bugfixes, will try again
2019-09-03 Trying again with RamFactor firmware
2019-09-05 Pipelined addition
2019-09-05 added some disassembly of RamFactor
2019-09-06 Clarified assignments
2019-09-08 Made AddrH high bit variable with mode input
2019-10-12 24-bit counter, CAS fixed
2019-10-13 Put gerber files back
2019-10-13 Register reset/initial values set syntax changed
2019-10-13 New schematic revision
2019-10-13 Switch library location, fixed datasheet fields
2019-10-14 Recompiled just to be sure
2019-10-18 New PLD revision
    For write operations, register data is latched and CAS signal becomes in the middle of S6, 70ns before the end of PHI0. This gives more write data setup time, which may be needed on the Apple II with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
2019-10-21 Fixed bugs in new PLD stuff
2019-12-21 Removed state counter reset
2020-01-26 Separated CSDBEN
2020-02-09 Removed AVR-JTAG-10 connector footprint
2020-02-16 Doesn't work but committing for posterity
2020-02-16 Fixed previous problem, working again
2020-02-17 Comments, no actual changes to CPLD verilog
2020-02-26 Removed SetWR and FullIOEN
2020-02-26 Moved REGEN and IOROMEN (no functional change)
2020-02-26 Removed inhibit output
2020-02-26 Cleanup
2020-02-26 Added separate configuration section
2020-02-26 Added transfer counters
2020-02-26 Put FullIOEN back
2020-03-10 Many changes
2020-10-08 Sketch of verilog
2020-10-08 Board done?
2020-10-25 reset button detect
2021-02-18 Fabbed
2021-03-15 Remove old CPLD stuff
2021-03-19 better
2021-03-19 before remove UFM
2021-04-03 Works?
2021-04-12 Update RAM Map
2021-04-18 Make apple boot
    Apple boots but SDRAM not working. Register R/W/increment works
2021-04-18 Remove CKE
2021-04-18 Sorta works
2021-04-19 Added CKE back
2021-04-20 Add "ZK, GF" to board
2021-04-20 Documentation update
2021-04-20 Works better?
2021-04-20 Latch config DIP switches at boot
    Also rearranged GR8RAM.v
2021-04-20 Updated slew rate/current strength assignments
2021-04-20 Revert "Updated slew rate/current strength assignments"
    This reverts commit 780fe32807977ad724567553cd7d3c217bb733fd.
2021-04-20 Revert "Updated slew rate/current strength assignments"
    This reverts commit 5db5490f52c8b2c1079f0477be8810ccdad10c5e.
2021-04-21 Output read data on falling edge to get more hold time
2021-04-21 Change IOROMEN logic back to synchronous reset
2021-04-22 Register Apple address bus on PHI0 rising edge
2021-04-22 Ignore Quartus stuff
2021-05-08 Update Initialization Sequence
2021-09-14 Release candidate?
2022-02-06 Migrate to KiCAD 6
2023-02-28 New project
2023-02-28 Compiled CPLD again
2023-03-06 Add back GR8RAM.bin
2024-02-17 Create new quartus project
2024-02-17 Untrack and delete .qws files
2024-02-17 Recompile
2024-02-17 Change ~ to ! where appropriate in GR8RAM.v
2024-03-13 rev. B boards almost done
2024-03-18 Adopt 0.5mm via-to-via spacing
2024-03-20 Done?
2024-03-25 Update version numbers
2024-03-29 1.0 RC
2024-05-12 Update gitignore -- remove lck and kicad_prl files
2024-05-13 Fix text size
2024-05-13 Firmware 1.0 RC1
2024-05-14 A.1.0 RC2/3
2024-05-23 Update Tag-Connect TC2050 footprint
2024-06-09 dip switch stuff
2024-07-28 Another board RC
2025-03-30 Lots?
2025-04-10 fix bom
2025-04-11 Update Makefile for KiCAD 9
2025-04-13 Update PCB text, etc
2025-04-13 B.1.0?

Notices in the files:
CPLD/MAXII/GR8RAM.qsf:
Copyright (C) 2019  Intel Corporation. All rights reserved.
